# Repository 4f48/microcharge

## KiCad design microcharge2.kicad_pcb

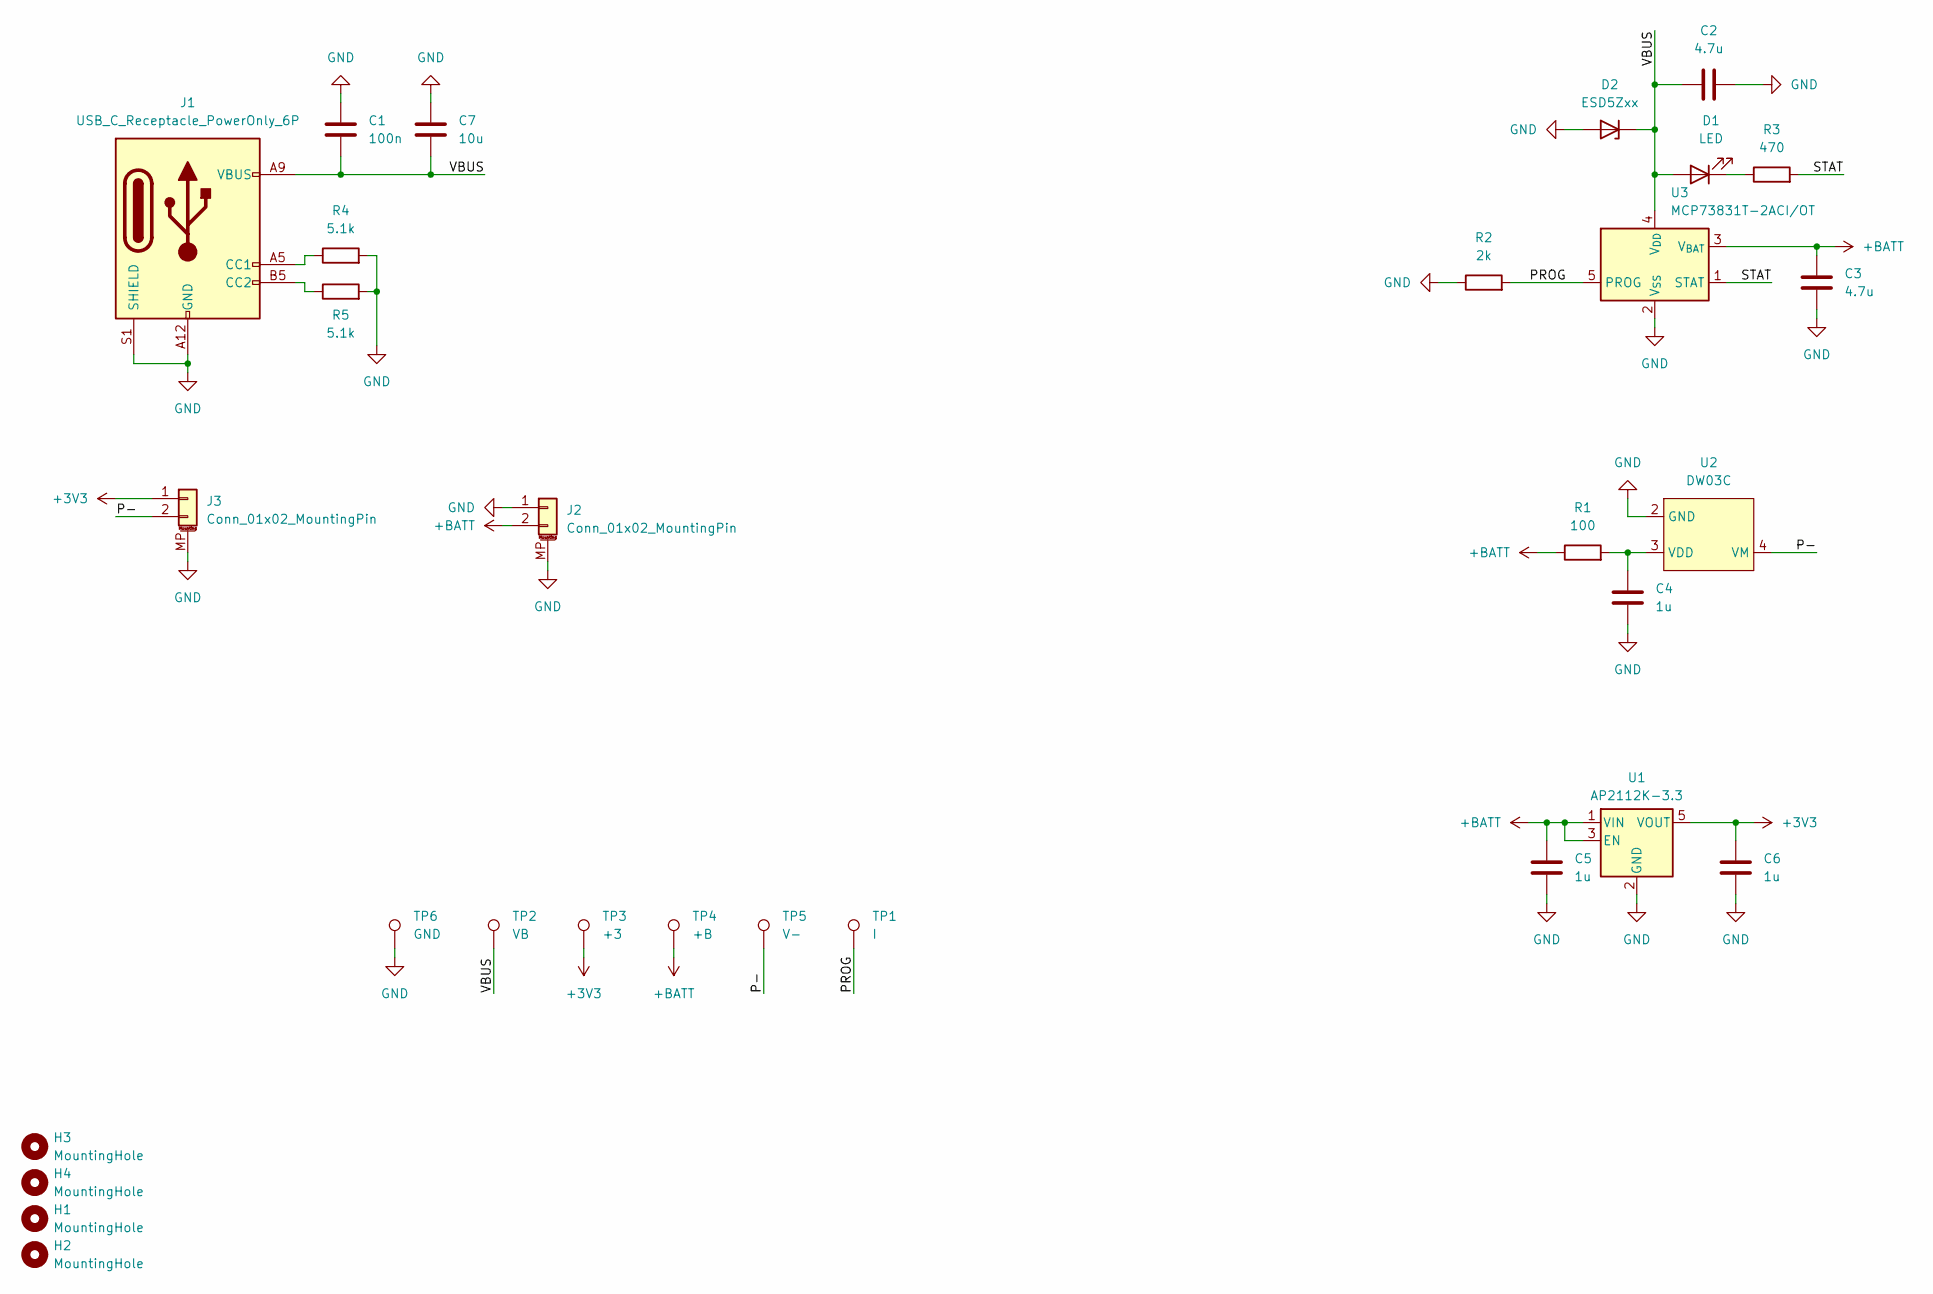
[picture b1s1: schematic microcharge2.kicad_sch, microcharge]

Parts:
C1: 100n; C_0603_1608Metric_Pad1.08x0.95mm_HandSolder; MPN CC0603KRX7R9BB104
C2, C3: 4.7u; C_0603_1608Metric_Pad1.08x0.95mm_HandSolder; MPN GRM188Z71A475ME15D
C4, C5, C6: 1u; C_0603_1608Metric_Pad1.08x0.95mm_HandSolder; MPN EMK107B7105KA-T
C7: 10u; C_0603_1608Metric_Pad1.08x0.95mm_HandSolder; MPN CL10A106MA8NRNC
D1: LED; LED_0603_1608Metric_Pad1.05x0.95mm_HandSolder; MPN 150060SS75000
D2: ESD5Zxx; D_SOD-523; MPN SZESD5Z5.0T5G
H1, H2, H3, H4: MountingHole; MountingHole_2.2mm_M2_ISO7380
J1: USB_C_Receptacle_PowerOnly_6P; USB_C_Receptacle_GCT_USB4135-GF-A_6P_TopMnt_Horizontal; MPN USB4135-GF-A
J2, J3: Conn_01x02_MountingPin; Molex_CLIK-Mate_502382-0270_1x02-1MP_P1.25mm_Vertical; MPN 5023820270
R1: 100; R_0603_1608Metric_Pad0.98x0.95mm_HandSolder; MPN RC0603JR-07100RL
R2: 2k; R_0603_1608Metric_Pad0.98x0.95mm_HandSolder; MPN RC0603FR-072KL
R3: 470; R_0603_1608Metric_Pad0.98x0.95mm_HandSolder; MPN RC0603JR-07470RL
R4, R5: 5.1k; R_0402_1005Metric_Pad0.72x0.64mm_HandSolder; MPN RC0402JR-135K1L
TP1: I; TestPoint_Pad_D1.0mm
TP2: VB; TestPoint_Pad_D1.0mm
TP3: +3; TestPoint_Pad_D1.0mm
TP4: +B; TestPoint_Pad_D1.0mm
TP5: V-; TestPoint_Pad_D1.0mm
TP6: GND; TestPoint_Pad_D1.0mm
U1: AP2112K-3.3; SOT-23-5_HandSoldering; MPN AP2112K-3.3TRG1
U2: DW03C; SOT-23-5_HandSoldering; MPN DW03C
U3: MCP73831T-2ACI/OT; SOT-23-5_HandSoldering; MPN MCP73831T-2ACI/OT

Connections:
+3V3: C6.1, J3.1, TP3.1, U1.5 (VOUT)
+BATT: C3.1, C5.1, J2.2, R1.1, TP4.1, U1.1 (VIN), U1.3 (EN), U3.3 (V_{BAT})
/P-: J3.2, TP5.1, U2.4 (VM), U2.5 (VM)
/PROG: R2.2, TP1.1, U3.5 (PROG)
/STAT: R3.2, U3.1 (STAT)
/VBUS: C1.2, C2.1, C7.2, D1.2 (A), D2.1 (K), J1.A9 (VBUS), J1.B9 (VBUS), TP2.1, U3.4 (V_{DD})
GND: C1.1, C2.2, C3.2, C4.2, C5.2, C6.2, C7.1, D2.2 (A), J1.A12 (GND), J1.B12 (GND), J1.S1 (SHIELD), J2.1, J2.MP (MountPin), J3.MP (MountPin), R2.1, R4.2, R5.2, TP6.1, U1.2 (GND), U2.2 (GND), U3.2 (V_{SS})
unnamed: D1.1 (K), R3.1
unnamed: J1.A5 (CC1), R4.1
unnamed: J1.B5 (CC2), R5.1
unnamed: C4.1, R1.2, U2.3 (VDD)

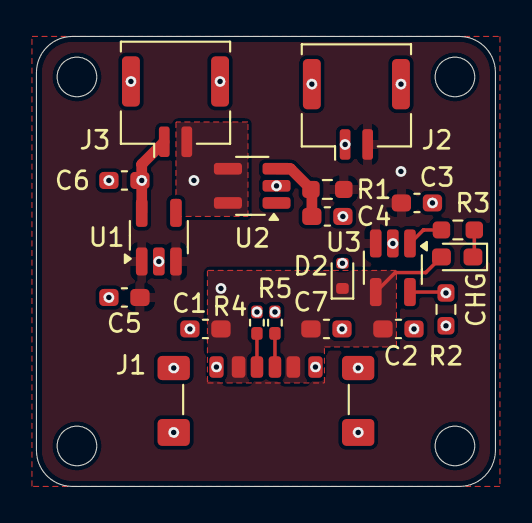
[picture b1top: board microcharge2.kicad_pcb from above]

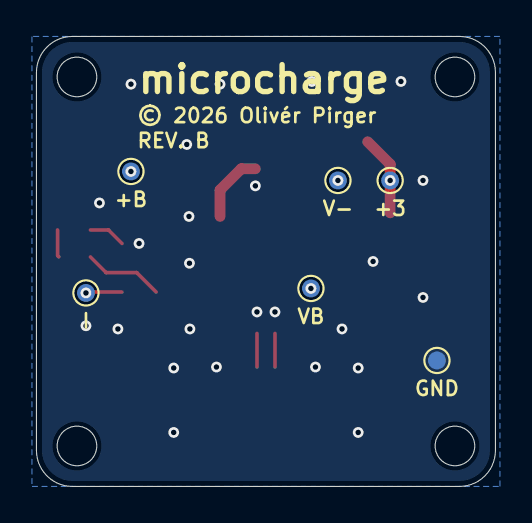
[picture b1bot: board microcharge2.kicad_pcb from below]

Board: 2 copper layers, 25.5 x 25.0 mm, 30 parts (6 on the bottom side), 11 nets.

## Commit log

2026-03-14 upload project

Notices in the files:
microcharge2.kicad_pcb:
© 2026 Olivér Pirger
